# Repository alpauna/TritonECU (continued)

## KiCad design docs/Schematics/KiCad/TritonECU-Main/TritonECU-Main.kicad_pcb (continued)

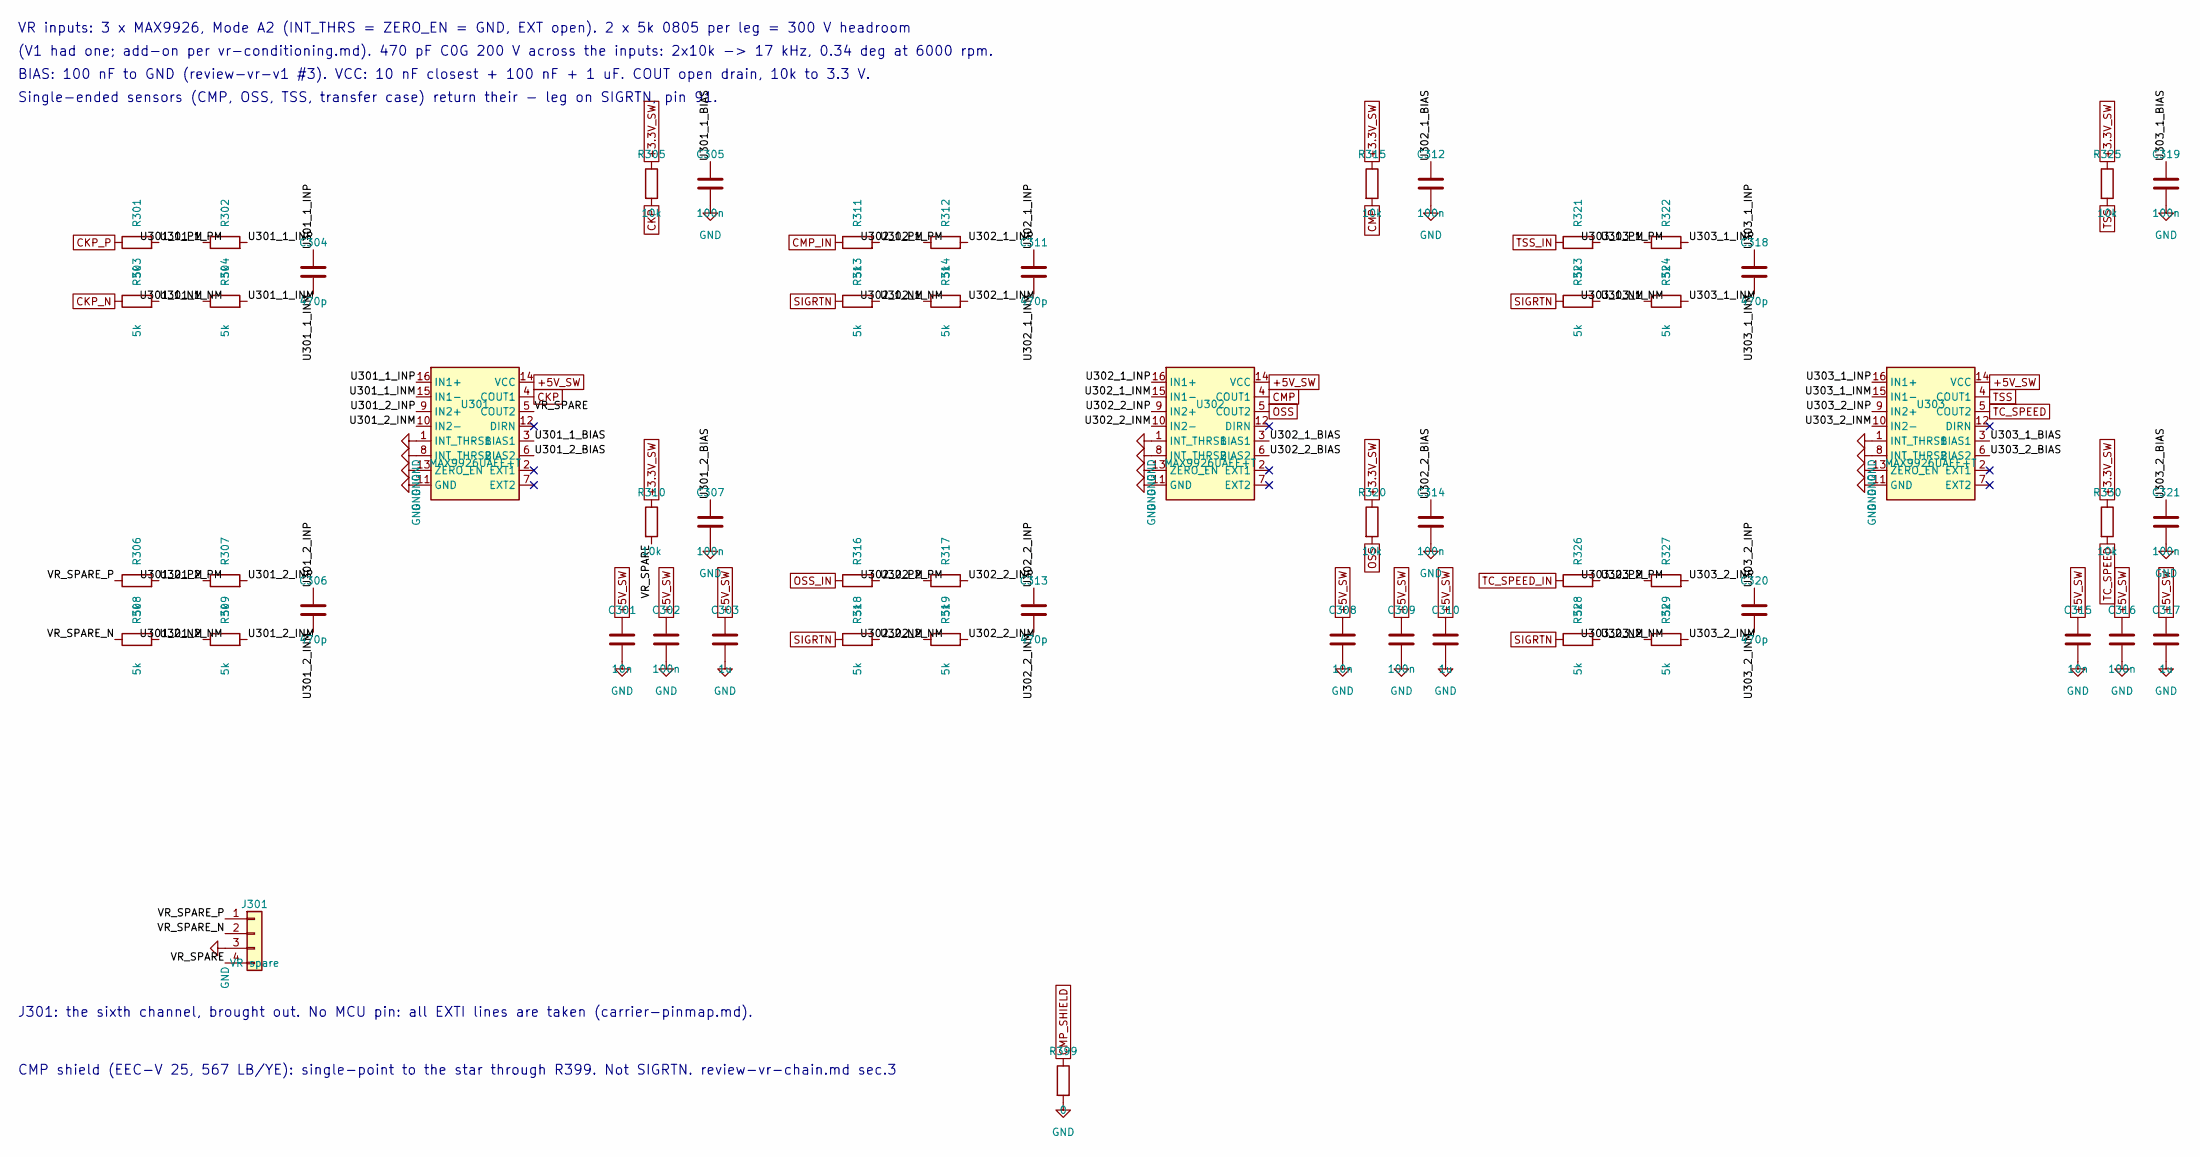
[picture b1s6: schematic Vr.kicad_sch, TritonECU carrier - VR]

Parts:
C301, C308, C315: 10n; C_0603_1608Metric_Pad1.08x0.95mm_HandSolder
C302, C305, C307, C309, C312, C314, C316, C319, C321: 100n; C_0603_1608Metric_Pad1.08x0.95mm_HandSolder
C303, C310, C317: 1u; C_0603_1608Metric_Pad1.08x0.95mm_HandSolder
C304, C306, C311, C313, C318, C320: 470p; C_0805_2012Metric_Pad1.18x1.45mm_HandSolder
J301: VR spare; PinHeader_1x04_P2.54mm_Vertical
R301, R302, R303, R304, R306, R307, R308, R309, R311, R312, R313, R314, R316, R317, R318, R319, R321, R322, R323, R324, R326, R327, R328, R329: 5k; R_0805_2012Metric_Pad1.20x1.40mm_HandSolder
R305, R310, R315, R320, R325, R330: 10k; R_0603_1608Metric_Pad0.98x0.95mm_HandSolder
R399: 0; R_0603_1608Metric_Pad0.98x0.95mm_HandSolder
U301, U302, U303: MAX9926UAEE+T; QSOP-16_3.9x4.9mm_P0.635mm

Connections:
+3.3V_SW: R305.1, R310.1, R315.1, R320.1, R325.1, R330.1; also elsewhere on the board
+5V_SW: C301.1, C302.1, C303.1, C308.1, C309.1, C310.1, C315.1, C316.1, C317.1, U301.14 (VCC), U302.14 (VCC), U303.14 (VCC); also elsewhere on the board
/VR/U301_1_BIAS: C305.1, U301.3 (BIAS1)
/VR/U301_1_INM: C304.2, R304.2, U301.15 (IN1-)
/VR/U301_1_INP: C304.1, R302.2, U301.16 (IN1+)
/VR/U301_1_NM: R303.2, R304.1
/VR/U301_1_PM: R301.2, R302.1
/VR/U301_2_BIAS: C307.1, U301.6 (BIAS2)
/VR/U301_2_INM: C306.2, R309.2, U301.10 (IN2-)
/VR/U301_2_INP: C306.1, R307.2, U301.9 (IN2+)
/VR/U301_2_NM: R308.2, R309.1
/VR/U301_2_PM: R306.2, R307.1
/VR/U302_1_BIAS: C312.1, U302.3 (BIAS1)
/VR/U302_1_INM: C311.2, R314.2, U302.15 (IN1-)
/VR/U302_1_INP: C311.1, R312.2, U302.16 (IN1+)
/VR/U302_1_NM: R313.2, R314.1
/VR/U302_1_PM: R311.2, R312.1
/VR/U302_2_BIAS: C314.1, U302.6 (BIAS2)
/VR/U302_2_INM: C313.2, R319.2, U302.10 (IN2-)
/VR/U302_2_INP: C313.1, R317.2, U302.9 (IN2+)
/VR/U302_2_NM: R318.2, R319.1
/VR/U302_2_PM: R316.2, R317.1
/VR/U303_1_BIAS: C319.1, U303.3 (BIAS1)
/VR/U303_1_INM: C318.2, R324.2, U303.15 (IN1-)
/VR/U303_1_INP: C318.1, R322.2, U303.16 (IN1+)
/VR/U303_1_NM: R323.2, R324.1
/VR/U303_1_PM: R321.2, R322.1
/VR/U303_2_BIAS: C321.1, U303.6 (BIAS2)
/VR/U303_2_INM: C320.2, R329.2, U303.10 (IN2-)
/VR/U303_2_INP: C320.1, R327.2, U303.9 (IN2+)
/VR/U303_2_NM: R328.2, R329.1
/VR/U303_2_PM: R326.2, R327.1
/VR/VR_SPARE: J301.4, R310.2, U301.5 (COUT2)
/VR/VR_SPARE_N: J301.2, R308.1
/VR/VR_SPARE_P: J301.1, R306.1
CKP: R305.2, U301.4 (COUT1); also elsewhere on the board
CKP_N: R303.1; also elsewhere on the board
CKP_P: R301.1; also elsewhere on the board
CMP: R315.2, U302.4 (COUT1); also elsewhere on the board
CMP_IN: R311.1; also elsewhere on the board
CMP_SHIELD: R399.1; also elsewhere on the board
GND: C301.2, C302.2, C303.2, C305.2, C307.2, C308.2, C309.2, C310.2, C312.2, C314.2, C315.2, C316.2, C317.2, C319.2, C321.2, J301.3, R399.2, U301.1 (INT_THRS1), U301.8 (INT_THRS2), U301.11 (GND), U301.13 (ZERO_EN), U302.1 (INT_THRS1), U302.8 (INT_THRS2), U302.11 (GND), U302.13 (ZERO_EN), U303.1 (INT_THRS1), U303.8 (INT_THRS2), U303.11 (GND), U303.13 (ZERO_EN); also elsewhere on the board
OSS: R320.2, U302.5 (COUT2); also elsewhere on the board
OSS_IN: R316.1; also elsewhere on the board
SIGRTN: R313.1, R318.1, R323.1, R328.1; also elsewhere on the board
TC_SPEED: R330.2, U303.5 (COUT2); also elsewhere on the board
TC_SPEED_IN: R326.1; also elsewhere on the board
TSS: R325.2, U303.4 (COUT1); also elsewhere on the board
TSS_IN: R321.1; also elsewhere on the board

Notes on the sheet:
VR inputs: 3 x MAX9926, Mode A2 (INT_THRS = ZERO_EN = GND, EXT open). 2 x 5k 0805 per leg = 300 V headroom
(V1 had one; add-on per vr-conditioning.md). 470 pF C0G 200 V across the inputs: 2x10k -> 17 kHz, 0.34 deg at 6000 rpm.
BIAS: 100 nF to GND (review-vr-v1 #3). VCC: 10 nF closest + 100 nF + 1 uF. COUT open drain, 10k to 3.3 V.
Single-ended sensors (CMP, OSS, TSS, transfer case) return their - leg on SIGRTN, pin 91.
J301: the sixth channel, brought out. No MCU pin: all EXTI lines are taken (carrier-pinmap.md).
CMP shield (EEC-V 25, 567 LB/YE): single-point to the star through R399. Not SIGRTN. review-vr-chain.md sec.3

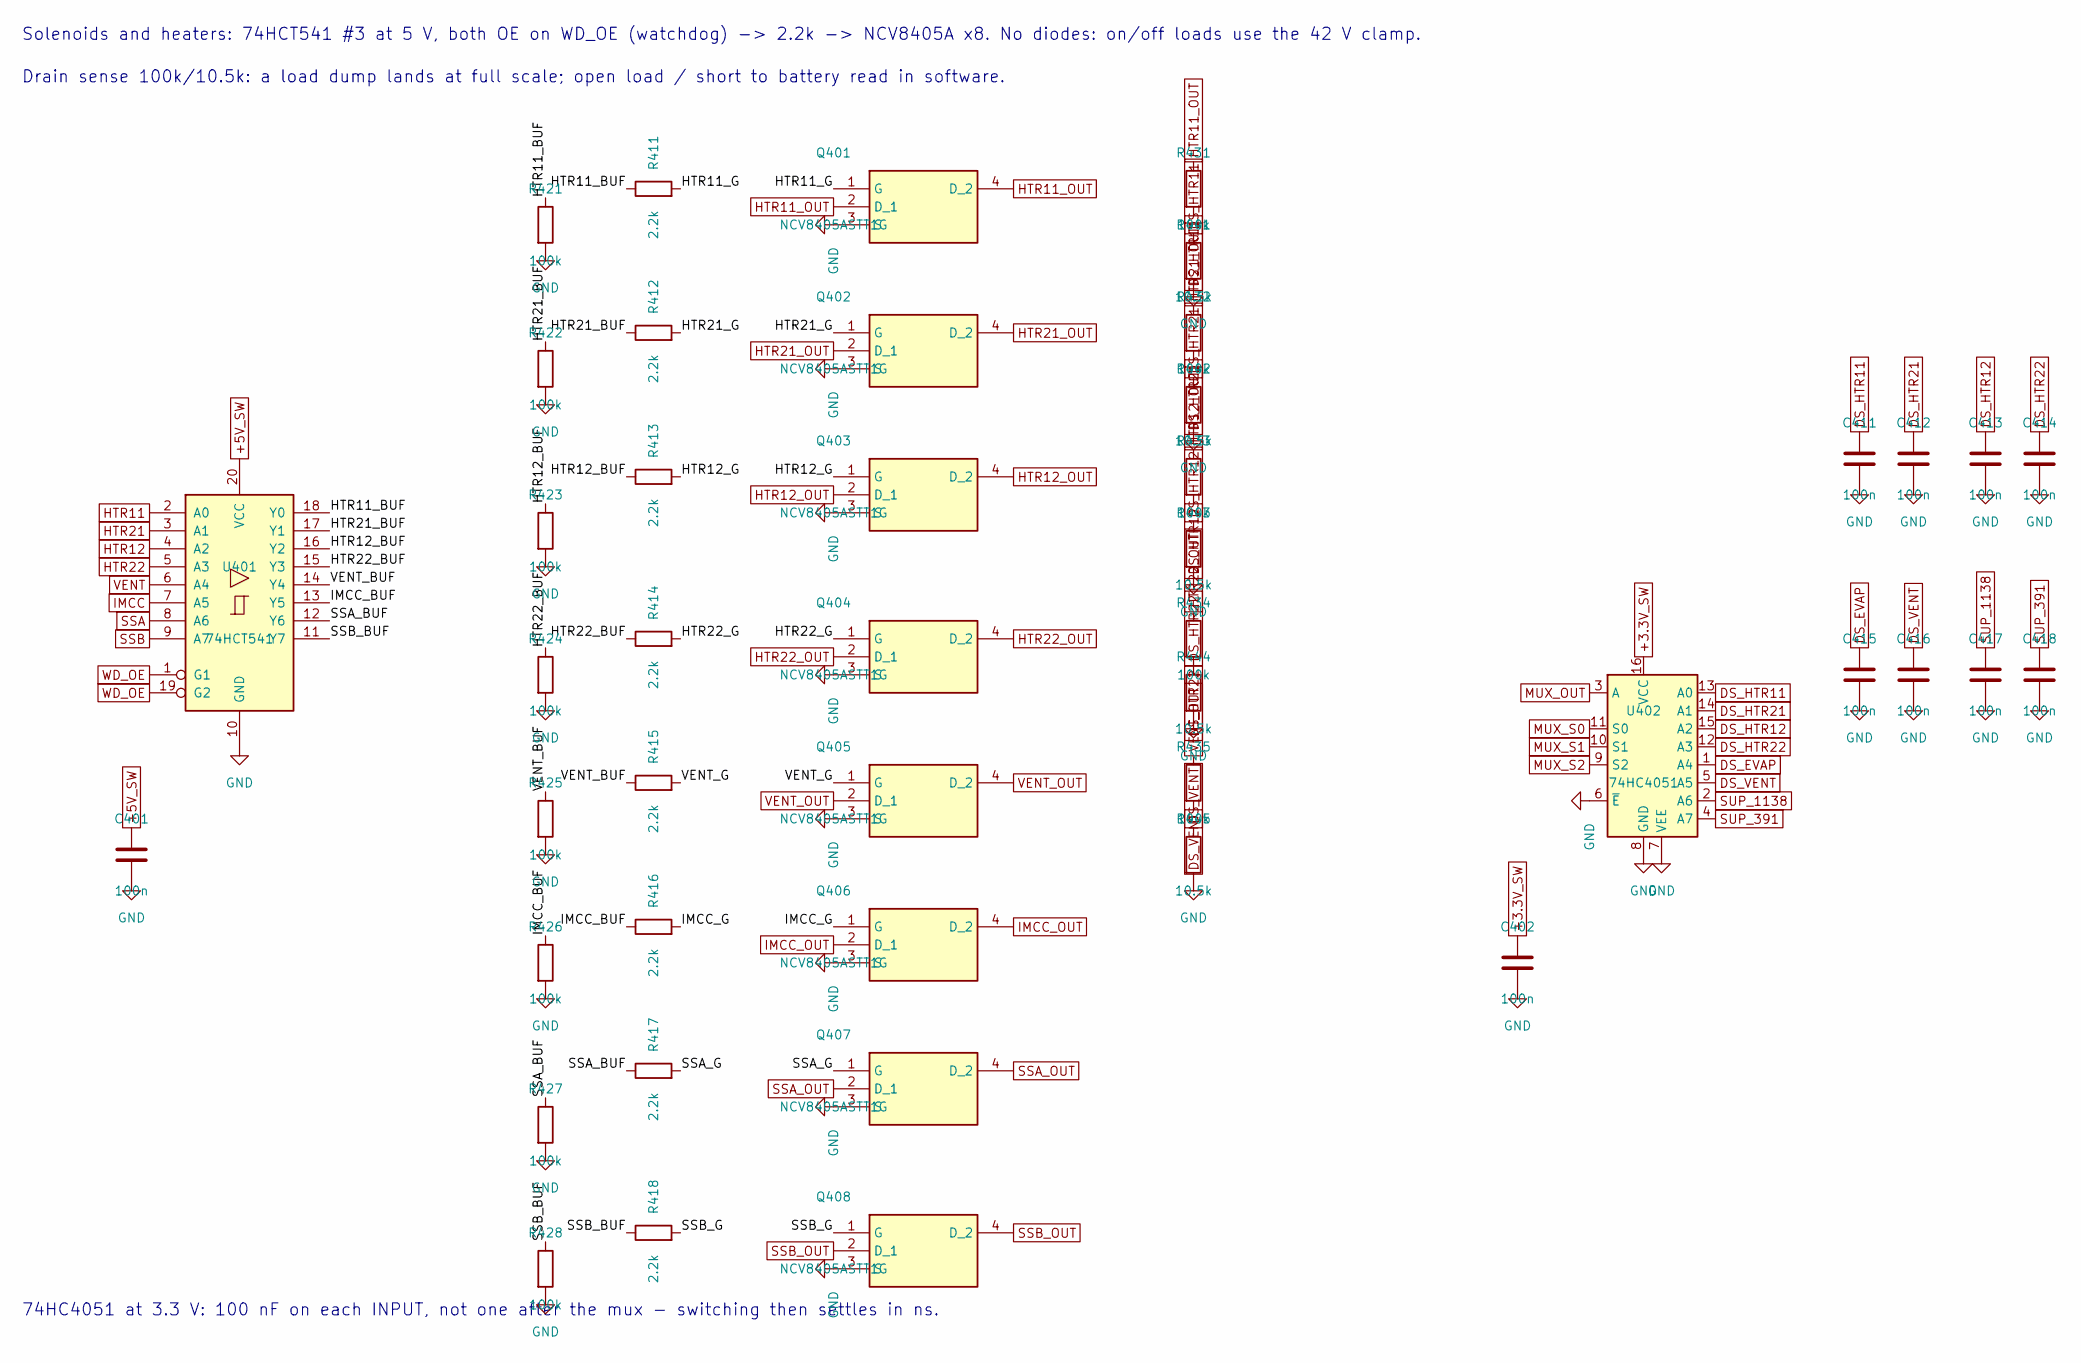
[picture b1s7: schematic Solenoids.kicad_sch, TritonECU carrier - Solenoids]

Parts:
C401, C402, C411, C412, C413, C414, C415, C416, C417, C418: 100n; C_0603_1608Metric_Pad1.08x0.95mm_HandSolder
Q401, Q402, Q403, Q404, Q405, Q406, Q407, Q408: NCV8405ASTT1G; SOT230P700X175-4N
R411, R412, R413, R414, R415, R416, R417, R418: 2.2k; R_0603_1608Metric_Pad0.98x0.95mm_HandSolder
R421, R422, R423, R424, R425, R426, R427, R428, R431, R432, R433, R434, R435: 100k; R_0603_1608Metric_Pad0.98x0.95mm_HandSolder
R441, R442, R443, R444, R445: 10.5k; R_0603_1608Metric_Pad0.98x0.95mm_HandSolder
U401: 74HCT541; SOIC-20W_7.5x12.8mm_P1.27mm
U402: 74HC4051; TSSOP-16_4.4x5mm_P0.65mm

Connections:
+3.3V_SW: C402.1, U402.16 (VCC); also elsewhere on the board
+5V_SW: C401.1, U401.20 (VCC); also elsewhere on the board
/Solenoids/HTR11_BUF: R411.1, R421.1, U401.18 (Y0)
/Solenoids/HTR11_G: Q401.1 (G), R411.2
/Solenoids/HTR12_BUF: R413.1, R423.1, U401.16 (Y2)
/Solenoids/HTR12_G: Q403.1 (G), R413.2
/Solenoids/HTR21_BUF: R412.1, R422.1, U401.17 (Y1)
/Solenoids/HTR21_G: Q402.1 (G), R412.2
/Solenoids/HTR22_BUF: R414.1, R424.1, U401.15 (Y3)
/Solenoids/HTR22_G: Q404.1 (G), R414.2
/Solenoids/IMCC_BUF: R416.1, R426.1, U401.13 (Y5)
/Solenoids/IMCC_G: Q406.1 (G), R416.2
/Solenoids/SSA_BUF: R417.1, R427.1, U401.12 (Y6)
/Solenoids/SSA_G: Q407.1 (G), R417.2
/Solenoids/SSB_BUF: R418.1, R428.1, U401.11 (Y7)
/Solenoids/SSB_G: Q408.1 (G), R418.2
/Solenoids/VENT_BUF: R415.1, R425.1, U401.14 (Y4)
/Solenoids/VENT_G: Q405.1 (G), R415.2
DS_EVAP: C415.1, U402.1 (A4); also elsewhere on the board
DS_HTR11: C411.1, R431.2, R441.1, U402.13 (A0)
DS_HTR12: C413.1, R433.2, R443.1, U402.15 (A2)
DS_HTR21: C412.1, R432.2, R442.1, U402.14 (A1)
DS_HTR22: C414.1, R434.2, R444.1, U402.12 (A3)
DS_VENT: C416.1, R435.2, R445.1, U402.5 (A5)
GND: C401.2, C402.2, C411.2, C412.2, C413.2, C414.2, C415.2, C416.2, C417.2, C418.2, Q401.3 (S), Q402.3 (S), Q403.3 (S), Q404.3 (S), Q405.3 (S), Q406.3 (S), Q407.3 (S), Q408.3 (S), R421.2, R422.2, R423.2, R424.2, R425.2, R426.2, R427.2, R428.2, R441.2, R442.2, R443.2, R444.2, R445.2, U401.10 (GND), U402.6 (~E), U402.7 (VEE), U402.8 (GND); also elsewhere on the board
HTR11: U401.2 (A0); also elsewhere on the board
HTR11_OUT: Q401.2 (D_1), Q401.4 (D_2), R431.1; also elsewhere on the board
HTR12: U401.4 (A2); also elsewhere on the board
HTR12_OUT: Q403.2 (D_1), Q403.4 (D_2), R433.1; also elsewhere on the board
HTR21: U401.3 (A1); also elsewhere on the board
HTR21_OUT: Q402.2 (D_1), Q402.4 (D_2), R432.1; also elsewhere on the board
HTR22: U401.5 (A3); also elsewhere on the board
HTR22_OUT: Q404.2 (D_1), Q404.4 (D_2), R434.1; also elsewhere on the board
IMCC: U401.7 (A5); also elsewhere on the board
IMCC_OUT: Q406.2 (D_1), Q406.4 (D_2); also elsewhere on the board
MUX_OUT: U402.3 (A); also elsewhere on the board
MUX_S0: U402.11 (S0); also elsewhere on the board
MUX_S1: U402.10 (S1); also elsewhere on the board
MUX_S2: U402.9 (S2); also elsewhere on the board
SSA: U401.8 (A6); also elsewhere on the board
SSA_OUT: Q407.2 (D_1), Q407.4 (D_2); also elsewhere on the board
SSB: U401.9 (A7); also elsewhere on the board
SSB_OUT: Q408.2 (D_1), Q408.4 (D_2); also elsewhere on the board
SUP_391: C418.1, U402.4 (A7); also elsewhere on the board
SUP_1138: C417.1, U402.2 (A6); also elsewhere on the board
VENT: U401.6 (A4); also elsewhere on the board
VENT_OUT: Q405.2 (D_1), Q405.4 (D_2), R435.1; also elsewhere on the board
WD_OE: U401.1 (G1), U401.19 (G2); also elsewhere on the board

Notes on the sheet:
Solenoids and heaters: 74HCT541 #3 at 5 V, both OE on WD_OE (watchdog) -> 2.2k -> NCV8405A x8. No diodes: on/off loads use the 42 V clamp.
Drain sense 100k/10.5k: a load dump lands at full scale; open load / short to battery read in software.
74HC4051 at 3.3 V: 100 nF on each INPUT, not one after the mux - switching then settles in ns.

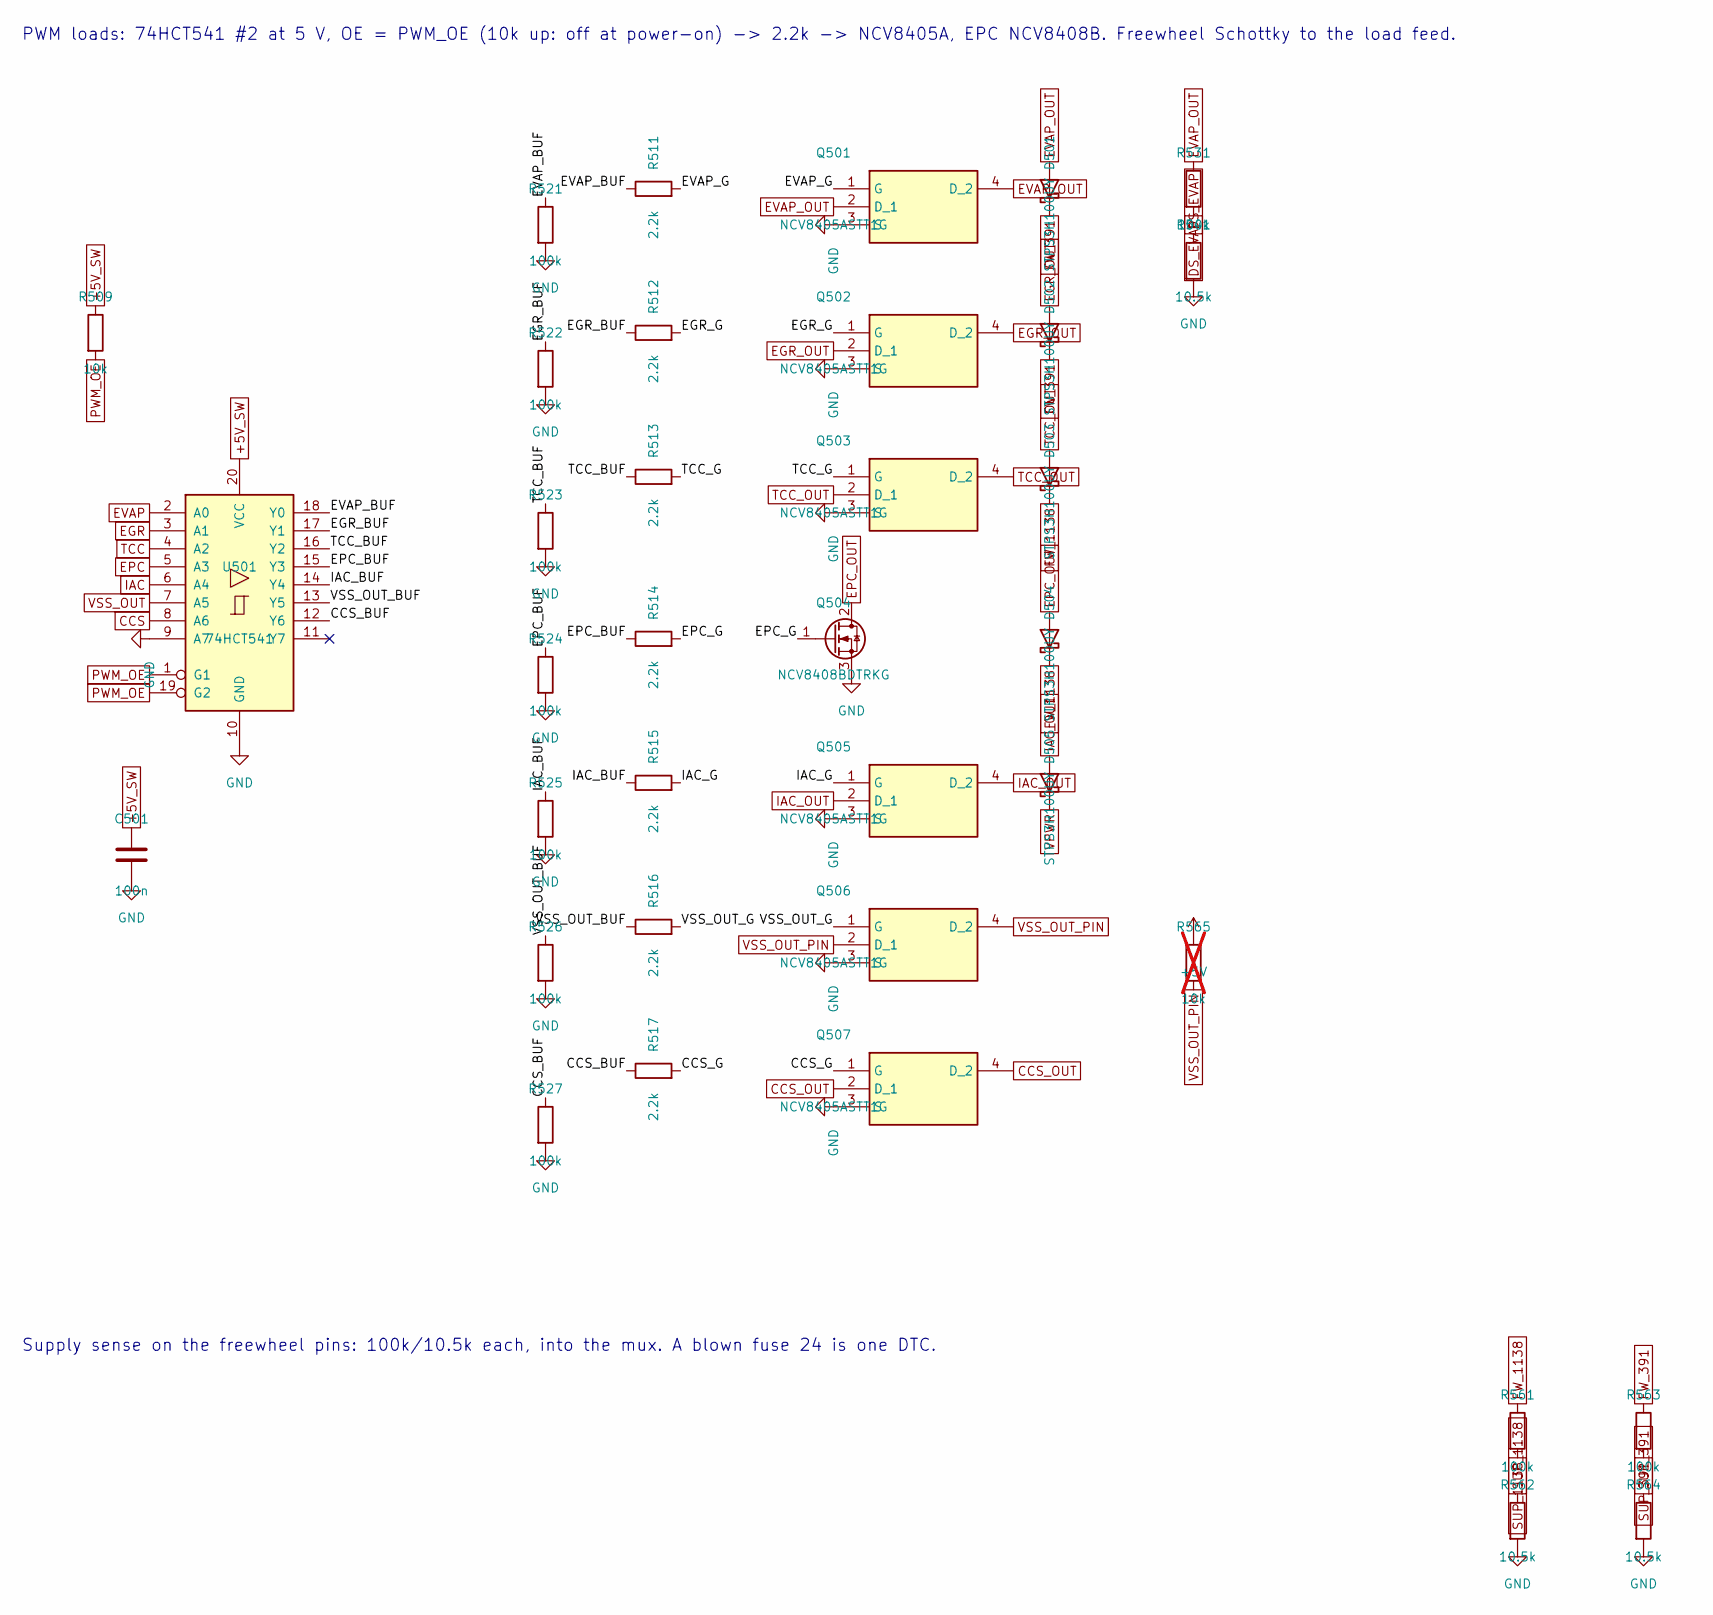
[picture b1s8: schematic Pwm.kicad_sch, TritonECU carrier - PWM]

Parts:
C501: 100n; C_0603_1608Metric_Pad1.08x0.95mm_HandSolder
D501, D502, D503, D504, D505: STPS3H100UY; D_SMB
Q501, Q502, Q503, Q505, Q506, Q507: NCV8405ASTT1G; SOT230P700X175-4N
Q504: NCV8408BDTRKG; TO-252-2
R509: 10k; R_0603_1608Metric_Pad0.98x0.95mm_HandSolder
R511, R512, R513, R514, R515, R516, R517: 2.2k; R_0603_1608Metric_Pad0.98x0.95mm_HandSolder
R521, R522, R523, R524, R525, R526, R527, R531, R561, R563: 100k; R_0603_1608Metric_Pad0.98x0.95mm_HandSolder
R541, R562, R564: 10.5k; R_0603_1608Metric_Pad0.98x0.95mm_HandSolder
R565: 10k; R_0603_1608Metric_Pad0.98x0.95mm_HandSolder; not fitted
U501: 74HCT541; SOIC-20W_7.5x12.8mm_P1.27mm

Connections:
+5V: R565.1; also elsewhere on the board
+5V_SW: C501.1, R509.1, U501.20 (VCC); also elsewhere on the board
/PWM/CCS_BUF: R517.1, R527.1, U501.12 (Y6)
/PWM/CCS_G: Q507.1 (G), R517.2
/PWM/EGR_BUF: R512.1, R522.1, U501.17 (Y1)
/PWM/EGR_G: Q502.1 (G), R512.2
/PWM/EPC_BUF: R514.1, R524.1, U501.15 (Y3)
/PWM/EPC_G: Q504.1 (G), R514.2
/PWM/EVAP_BUF: R511.1, R521.1, U501.18 (Y0)
/PWM/EVAP_G: Q501.1 (G), R511.2
/PWM/IAC_BUF: R515.1, R525.1, U501.14 (Y4)
/PWM/IAC_G: Q505.1 (G), R515.2
/PWM/TCC_BUF: R513.1, R523.1, U501.16 (Y2)
/PWM/TCC_G: Q503.1 (G), R513.2
/PWM/VSS_OUT_BUF: R516.1, R526.1, U501.13 (Y5)
/PWM/VSS_OUT_G: Q506.1 (G), R516.2
CCS: U501.8 (A6); also elsewhere on the board
CCS_OUT: Q507.2 (D_1), Q507.4 (D_2); also elsewhere on the board
DS_EVAP: R531.2, R541.1; also elsewhere on the board
EGR: U501.3 (A1); also elsewhere on the board
EGR_OUT: D502.2 (A), Q502.2 (D_1), Q502.4 (D_2); also elsewhere on the board
EPC: U501.5 (A3); also elsewhere on the board
EPC_OUT: D504.2 (A), Q504.2 (D); also elsewhere on the board
EVAP: U501.2 (A0); also elsewhere on the board
EVAP_OUT: D501.2 (A), Q501.2 (D_1), Q501.4 (D_2), R531.1; also elsewhere on the board
FW_391: D501.1 (K), D502.1 (K), R563.1; also elsewhere on the board
FW_1138: D503.1 (K), D504.1 (K), R561.1; also elsewhere on the board
GND: C501.2, Q501.3 (S), Q502.3 (S), Q503.3 (S), Q504.3 (S), Q505.3 (S), Q506.3 (S), Q507.3 (S), R521.2, R522.2, R523.2, R524.2, R525.2, R526.2, R527.2, R541.2, R562.2, R564.2, U501.9 (A7), U501.10 (GND); also elsewhere on the board
IAC: U501.6 (A4); also elsewhere on the board
IAC_OUT: D505.2 (A), Q505.2 (D_1), Q505.4 (D_2); also elsewhere on the board
PWM_OE: R509.2, U501.1 (G1), U501.19 (G2); also elsewhere on the board
SUP_391: R563.2, R564.1; also elsewhere on the board
SUP_1138: R561.2, R562.1; also elsewhere on the board
TCC: U501.4 (A2); also elsewhere on the board
TCC_OUT: D503.2 (A), Q503.2 (D_1), Q503.4 (D_2); also elsewhere on the board
VPWR: D505.1 (K); also elsewhere on the board
VSS_OUT: U501.7 (A5); also elsewhere on the board
VSS_OUT_PIN: Q506.2 (D_1), Q506.4 (D_2), R565.2; also elsewhere on the board

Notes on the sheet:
PWM loads: 74HCT541 #2 at 5 V, OE = PWM_OE (10k up: off at power-on) -> 2.2k -> NCV8405A, EPC NCV8408B. Freewheel Schottky to the load feed.
Supply sense on the freewheel pins: 100k/10.5k each, into the mux. A blown fuse 24 is one DTC.

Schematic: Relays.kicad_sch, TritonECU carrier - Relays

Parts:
C601: 100n; C_0805_2012Metric_Pad1.18x1.45mm_HandSolder
F601, F602, F603, F604: MF-MSMF030/60-2; Fuse_1812_4532Metric
R601, R602, R603, R604: 100k; R_0603_1608Metric_Pad0.98x0.95mm_HandSolder
U601: TBD62083AFNG; SOP65P640X155-18N

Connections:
/Relays/ACC_SINK: F604.1, U601.15 (O4)
/Relays/FAN1_SINK: F602.1, U601.17 (O2)
/Relays/FAN2_SINK: F603.1, U601.16 (O3)
/Relays/FPUMP_SINK: F601.1, U601.18 (O1)
ACC: R604.1, U601.4 (I4); also elsewhere on the board
ACC_OUT: F604.2; also elsewhere on the board
FAN1: R602.1, U601.2 (I2); also elsewhere on the board
FAN1_OUT: F602.2; also elsewhere on the board
FAN2: R603.1, U601.3 (I3); also elsewhere on the board
FAN2_OUT: F603.2; also elsewhere on the board
FPUMP: R601.1, U601.1 (I1); also elsewhere on the board
FPUMP_OUT: F601.2; also elsewhere on the board
GND: C601.2, R601.2, R602.2, R603.2, R604.2, U601.5 (I5), U601.6 (I6), U601.7 (I7), U601.8 (I8), U601.9 (GND); also elsewhere on the board
VBAT_SENSE: C601.1, U601.10 (COMMON); also elsewhere on the board

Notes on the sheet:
Relays: TBD62083AFNG, direct from GPIO. 100k pulldown holds every relay off through reset.
COMMON = permanent B+ (EEC-V 55, 729 RD/WH, CJB 5 A): every coil feed is at or below it, so no channel
back-feeds. [CONFIRM] sharing pin 55 with the battery-sense divider: clamp current is only the coil decay.
PTC in series: the array has no current limit, so a shorted coil is stopped by F60x. Coil currents [CONFIRM] on the truck.
Channels 5-8 spare: inputs to GND, outputs open. No MCU pins left for them (carrier-pinmap.md).

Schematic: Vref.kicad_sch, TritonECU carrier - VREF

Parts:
C701: 1u; C_0805_2012Metric_Pad1.18x1.45mm_HandSolder
C702, C704, C705, C706: 100n; C_0603_1608Metric_Pad1.08x0.95mm_HandSolder
C703: 22u; C_1206_3216Metric_Pad1.33x1.80mm_HandSolder
C707: 100n; C_0603_1608Metric_Pad1.08x0.95mm_HandSolder; not fitted
C708: 22n; C_0603_1608Metric_Pad1.08x0.95mm_HandSolder
C709: 22n; C_0603_1608Metric_Pad1.08x0.95mm_HandSolder; not fitted
C710: 10n; C_0603_1608Metric_Pad1.08x0.95mm_HandSolder
D701: SMAJ24CA; D_SMA
D702: SMAJ24CA; D_SMA; not fitted
D703, D704: BAT54J; D_SOD-323F
Q701: DMN6040SVTQ-7; SOT95P280X100-6N
Q702: DMN6040SVTQ-7; SOT95P280X100-6N; not fitted
R701, R708: 100k; R_0603_1608Metric_Pad0.98x0.95mm_HandSolder
R702, R703, R704: 10k; R_0603_1608Metric_Pad0.98x0.95mm_HandSolder
R705: 2.2k; R_0603_1608Metric_Pad0.98x0.95mm_HandSolder
R706: 4.7k; R_0603_1608Metric_Pad0.98x0.95mm_HandSolder
R707: 8.06k; R_0603_1608Metric_Pad0.98x0.95mm_HandSolder
R709: 12.4k; R_0603_1608Metric_Pad0.98x0.95mm_HandSolder
TP701: VREF2; TestPoint_Pad_D1.5mm; not fitted
U701: NCV8772CDT504RKG; TO-252-5_TabPin3
U702: TPS2H160BQPWPRQ1; SOP65P640X120-17N
U703: LM74700QDBVRQ1; SOT-23-6
U704: LM74700QDBVRQ1; SOT-23-6; not fitted

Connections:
+3.3V: D703.1 (K), D704.1 (K); also elsewhere on the board
+3.3V_SW: R704.1; also elsewhere on the board
/VREF/VREF1_G: Q701.3 (G), U703.5 (GATE)
/VREF/VREF1_SW: C706.2, C708.1, Q701.4 (S), U702.15 (OUT1_1), U702.16 (OUT1_2), U703.3 (EN), U703.6 (ANODE)
/VREF/VREF1_VCAP: C706.1, U703.1 (VCAP)
/VREF/VREF2: D702.1 (A1), Q702.1 (D_1), Q702.2 (D_2), Q702.5 (D_3), Q702.6 (D_4), TP701.1, U704.4 (CATHODE)
/VREF/VREF2_G: Q702.3 (G), U704.5 (GATE)
/VREF/VREF2_SW: C707.2, C709.1, Q702.4 (S), U702.11 (OUT2_1), U702.12 (OUT2_2), U704.3 (EN), U704.6 (ANODE)
/VREF/VREF2_VCAP: C707.1, U704.1 (VCAP)
/VREF/VREF_CL: R707.1, U702.7 (CL)
/VREF/VREF_CS_RAW: R705.1, R706.1, U702.6 (CS)
/VREF/VREF_DIAG: R702.2, U702.3 (DIAG_EN)
/VREF/VREF_THER: R703.2, U702.9 (THER)
GND: C701.2, C702.2, C703.2, C704.2, C705.2, C708.2, C709.2, C710.2, D701.2 (A2), D702.2 (A2), R701.2, R705.2, R707.2, R709.2, U701.3 (GND), U702.8 (GND), U702.17 (EP), U703.2 (GND), U704.2 (GND); also elsewhere on the board
VPROT: C701.1, C702.1, U701.1 (VIN); also elsewhere on the board
VREF: D701.1 (A1), Q701.1 (D_1), Q701.2 (D_2), Q701.5 (D_3), Q701.6 (D_4), R708.1, U703.4 (CATHODE); also elsewhere on the board
VREF_5V: C703.1, C704.1, C705.1, R702.1, R703.1, U701.5 (VOUT), U702.13 (VS_1), U702.14 (VS_2); also elsewhere on the board
VREF_CS: D703.2 (A), R706.2; also elsewhere on the board
VREF_EN: R701.1, U701.4 (EN); also elsewhere on the board
VREF_FAULT: R704.2, U702.4 (~FAULT); also elsewhere on the board
VREF_IN1: U702.1 (IN1); also elsewhere on the board
VREF_IN2: U702.2 (IN2); also elsewhere on the board
VREF_SEL: U702.5 (SEL); also elsewhere on the board
VREF_STB: C710.1, D704.2 (A), R708.2, R709.1; also elsewhere on the board

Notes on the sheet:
VREF: NCV8772C 5.00 V on VPROT (the LTC4364 output, not the 5 V buck-boost), EN under MCU control.
TPS2H160B-Q1: RCL 8.06k = 248 mA per feed; RCS 2.2k (2.5 V linear ceiling at VS = 5 V); THER high = latch.
LM74700-Q1 + DMN6040 (VGS +-20 V) blocks a short to battery; SMAJ24CA stands off 24 V, transients only. No PPTC.
Firmware sheds a faulted channel (t_CL deg 80-180 us), retries seconds apart. Hold IN1/IN2/SEL low while EN is low.
VREF_5V is the ratiometric divisor: the ADS8588H senses it here, one channel for both feeds.
Channel 2 (U704, Q702, D702, TP701) not fitted: this truck has one VREF pin, 90. Never enable IN2.
Short to battery: 100k/12.4k from the feed. 5 V -> 0.55 V, 14 V -> 1.54 V, 27 V -> 2.98 V. Returns to the ADC ground.

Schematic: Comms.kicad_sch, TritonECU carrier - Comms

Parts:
C901, C903, C904, C905, C907, C914: 100n; C_0603_1608Metric_Pad1.08x0.95mm_HandSolder
C902, C909, C911: 1u; C_0603_1608Metric_Pad1.08x0.95mm_HandSolder
C906, C913: 4.7u; C_0805_2012Metric_Pad1.18x1.45mm_HandSolder
C908, C910: 4.7n; C_0603_1608Metric_Pad1.08x0.95mm_HandSolder
C912: 1n; C_0603_1608Metric_Pad1.08x0.95mm_HandSolder
D901, D905: NUP2105L; SOT-23
D902, D903: MM3Z3V3BW; D_SOD-323F
D904: SMF3.3A; D_SMF
J901: USB4105-GF-A; USB_C_Receptacle_GCT_USB4105-xx-A_16P_TopMnt_Horizontal
J902: 104031-0811; microSD_HC_Molex_104031-0811
R901: 10k; R_0603_1608Metric_Pad0.98x0.95mm_HandSolder
R902, R903, R909, R918: 100; R_0603_1608Metric_Pad0.98x0.95mm_HandSolder
R904, R905, R906, R907, R919: 100k; R_0603_1608Metric_Pad0.98x0.95mm_HandSolder
R908: 4.7M; R_0603_1608Metric_Pad0.98x0.95mm_HandSolder
R910: 0; R_0603_1608Metric_Pad0.98x0.95mm_HandSolder
R911, R912: 60.4; R_1206_3216Metric_Pad1.30x1.75mm_HandSolder
R913, R914: 5.1k; R_0603_1608Metric_Pad0.98x0.95mm_HandSolder
R915: 15k; R_0603_1608Metric_Pad0.98x0.95mm_HandSolder
R916: 27k; R_0603_1608Metric_Pad0.98x0.95mm_HandSolder
R917: 1M; R_0603_1608Metric_Pad0.98x0.95mm_HandSolder
R920: 22; R_0603_1608Metric_Pad0.98x0.95mm_HandSolder
R921, R922, R923, R924, R925: 47k; R_0603_1608Metric_Pad0.98x0.95mm_HandSolder
U901: DRV8837DSGR; Texas_DSG0008A_WSON-8-1EP_2x2mm_P0.5mm_EP0.9x1.6mm
U902: TLV7031DBVR; SOT-23-5
U903: TJA1042T/3; SOIC-8_3.9x4.9mm_P1.27mm
U904: USBLC6-2SC6; SOT-23-6
U905: TPS22917DBVR; SOT-23-6

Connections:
+3.3V: C903.1, C904.1, C907.1, C911.1, U901.8 (VCC), U902.5 (V+), U903.5 (VIO), U905.1 (VIN); also elsewhere on the board
+5V: C901.1, C902.1, C905.1, C906.1, U901.1 (VM), U903.3 (VCC); also elsewhere on the board
/Comms/CAN_SPLIT: C908.1, R911.2, R912.1
/Comms/SCP_CMP: R908.1, R909.1, U902.1
/Comms/SCP_RXN: D903.1 (K), R906.2, R907.1, U902.4 (-)
/Comms/SCP_RXP: D902.1 (K), R904.2, R905.1, R908.2, U902.3 (+)
/Comms/SCP_TXN: R903.1, U901.3 (OUT2)
/Comms/SCP_TXP: R902.1, U901.2 (OUT1)
/Comms/SD_3V3: C913.1, C914.1, J902.4 (VDD), R918.2, R921.1, R922.1, R923.1, R924.1, R925.1, U905.6 (VOUT)
/Comms/SD_CLK: J902.5 (CLK), R920.2
/Comms/SD_CT: C912.1, U905.4 (CT)
/Comms/SD_D1: J902.8 (DAT1), R923.2
/Comms/SD_D2: J902.1 (DAT2), R924.2
/Comms/SD_D3: J902.2 (DAT3/CD), R925.2
/Comms/SD_QOD: R918.1, U905.5 (QOD)
/Comms/USB_CC1: J901.A5 (CC1), R913.1
/Comms/USB_CC2: J901.B5 (CC2), R914.1
/Comms/USB_SHIELD: C910.1, J901.SH (SHIELD), R917.1
/Comms/USB_VBUS_C: C909.1, J901.A4 (VBUS), J901.A9 (VBUS), J901.B4 (VBUS), J901.B9 (VBUS), R915.1, U904.5 (VBUS)
CAN_H: D905.1 (K), R911.1, U903.7 (CANH); also elsewhere on the board
CAN_L: D905.2 (K), R912.2, U903.6 (CANL); also elsewhere on the board
CAN_RX: R910.1, U903.4 (RXD); also elsewhere on the board
CAN_RX_WAKE: R910.2; also elsewhere on the board
CAN_STB: U903.8 (STB); also elsewhere on the board
CAN_TX: U903.1 (TXD); also elsewhere on the board
GND: C901.2, C902.2, C903.2, C904.2, C905.2, C906.2, C907.2, C908.2, C909.2, C910.2, C911.2, C912.2, C913.2, C914.2, D901.3 (A), D902.2 (A), D903.2 (A), D904.2 (A), D905.3 (A), J901.A1 (GND), J901.A12 (GND), J901.B1 (GND), J901.B12 (GND), J902.6 (VSS), J902.SH (SHIELD), R901.2, R905.2, R907.2, R913.2, R914.2, R916.2, R917.2, R919.2, U901.4 (GND), U901.9 (GND), U902.2 (V-), U903.2 (GND), U904.2 (GND), U905.2 (GND); also elsewhere on the board
J1850_NSLEEP: R901.1, U901.7 (~SLEEP); also elsewhere on the board
J1850_RX: D904.1 (K), R909.2; also elsewhere on the board
J1850_TXN: U901.5 (IN2); also elsewhere on the board
J1850_TXP: U901.6 (IN1); also elsewhere on the board
SCP_N: D901.2 (K), R903.2, R906.1; also elsewhere on the board
SCP_P: D901.1 (K), R902.2, R904.1; also elsewhere on the board
SD_CK: R920.1; also elsewhere on the board
SD_CMD: J902.3 (CMD), R921.2; also elsewhere on the board
SD_D0: J902.7 (DAT0), R922.2; also elsewhere on the board
SD_PWR_EN: R919.1, U905.3 (ON); also elsewhere on the board
USB_DM: J901.A7 (D-), J901.B7 (D-), U904.3 (I/O2), U904.4 (I/O2); also elsewhere on the board
USB_DP: J901.A6 (D+), J901.B6 (D+), U904.1 (I/O1), U904.6 (I/O1); also elsewhere on the board
USB_VBUS: R915.2, R916.1; also elsewhere on the board

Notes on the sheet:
SCP (J1850 PWM, EEC-V 16 = SCP+, 15 = SCP-): DRV8837 drives, TLV7031 receives. Passive state is IN1 = IN2 = LOW (coast,
Hi-Z) so another node can win arbitration; nSLEEP 10k low releases the whole bus at power-on. 100R per TX line.
RX divider 100k:100k BOTH to GND (not 10k:100k, not to 3.3 V: the two OpenJ1850 traps), MM3Z3V3 clamps, 4.7M hysteresis.
CAN (private, to the dash display; EEC-V 42 = CAN_H, 43 = CAN_L, terminals added): TJA1042T/3, 10 uA standby.
RXD goes to CAN1_RX (PD0) AND to PA0/WKUP1 through R9xx: Standby wakes only on a WKUP pin. STB has an internal pull-up.
TERMINATION - this ECU is a bus END. Split, matched 1 %: 2 x 60.4R + 4.7n. A THIRD node must NOT terminate.
USB-C, device only (tuning, flashing): 5.1k on CC1/CC2, USBLC6-2SC6, VBUS sensed only (never powers the ECU).
microSD, SDMMC2 1-bit. Card power through TPS22917 on SD_PWR_EN (100k down): 3.3 V is always on and an idle
card alone is ~100 uA against the 184 uA parked budget. Pull-ups go to the CARD rail so nothing back-powers it. No CD pin.
DAT3 pulled up keeps the card in SD mode (low at CMD0 selects SPI). DAT1/DAT2 unused in 1-bit, pulled up.

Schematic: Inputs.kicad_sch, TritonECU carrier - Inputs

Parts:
C1001, C1002, C1003, C1004, C1005, C1006, C1007, C1008: 10n; C_0603_1608Metric_Pad1.08x0.95mm_HandSolder
C1009: 100n; C_0603_1608Metric_Pad1.08x0.95mm_HandSolder
D1001, D1003, D1005, D1007, D1009, D1011, D1013, D1015: SMF24A; D_SMF
D1002, D1004, D1006, D1008, D1010, D1012, D1014, D1016, D1017: BAT54J; D_SOD-323F
J1001: TACH/SPEED; PinHeader_1x03_P2.54mm_Vertical
JP1001: BOOT0 DFU; SolderJumper-2_P1.3mm_Open_RoundedPad1.0x1.5mm
R1001, R1004, R1007, R1010: 4.7k; R_0805_2012Metric_Pad1.20x1.40mm_HandSolder
R1002, R1005, R1008, R1011, R1014, R1017, R1020, R1023, R1025: 33k; R_0805_2012Metric_Pad1.20x1.40mm_HandSolder
R1003, R1006, R1009, R1012, R1015, R1018, R1021, R1024, R1026: 15k; R_0603_1608Metric_Pad0.98x0.95mm_HandSolder
R1013, R1016, R1019, R1022: 4.7k; R_0805_2012Metric_Pad1.20x1.40mm_HandSolder; not fitted
R1027, R1028: 220; R_0603_1608Metric_Pad0.98x0.95mm_HandSolder

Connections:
4X4L: C1004.1, D1008.2 (A), R1011.2, R1012.1; also elsewhere on the board
4X4L_IN: D1007.1 (K), R1010.2, R1011.1; also elsewhere on the board
+3.3V: D1002.1 (K), D1004.1 (K), D1006.1 (K), D1008.1 (K), D1010.1 (K), D1012.1 (K), D1014.1 (K), D1016.1 (K), D1017.1 (K), JP1001.1 (A); also elsewhere on the board
/Inputs/SPEED_H: J1001.2, R1028.2
/Inputs/TACH_H: J1001.1, R1027.2
ACP: C1007.1, D1014.2 (A), R1020.2, R1021.1; also elsewhere on the board
ACP_IN: D1013.1 (K), R1019.2, R1020.1; also elsewhere on the board
BOOT0: JP1001.2 (B); also elsewhere on the board
BRAKE: C1006.1, D1012.2 (A), R1017.2, R1018.1; also elsewhere on the board
BRAKE_IN: D1011.1 (K), R1016.2, R1017.1; also elsewhere on the board
GND: C1001.2, C1002.2, C1003.2, C1004.2, C1005.2, C1006.2, C1007.2, C1008.2, C1009.2, D1001.2 (A), D1003.2 (A), D1005.2 (A), D1007.2 (A), D1009.2 (A), D1011.2 (A), D1013.2 (A), D1015.2 (A), J1001.3, R1003.2, R1006.2, R1009.2, R1012.2, R1015.2, R1018.2, R1021.2, R1024.2, R1026.2; also elsewhere on the board
IGN_WAKE: C1009.1, D1017.2 (A), R1025.2, R1026.1; also elsewhere on the board
SPEED: R1028.1; also elsewhere on the board
TACH: R1027.1; also elsewhere on the board
TCS: C1008.1, D1016.2 (A), R1023.2, R1024.1; also elsewhere on the board
TCS_IN: D1015.1 (K), R1022.2, R1023.1; also elsewhere on the board
TR1: C1001.1, D1002.2 (A), R1002.2, R1003.1; also elsewhere on the board
TR1_IN: D1001.1 (K), R1001.2, R1002.1; also elsewhere on the board
TR2: C1002.1, D1004.2 (A), R1005.2, R1006.1; also elsewhere on the board
TR2_IN: D1003.1 (K), R1004.2, R1005.1; also elsewhere on the board
TR3A: C1005.1, D1010.2 (A), R1014.2, R1015.1; also elsewhere on the board
TR3A_IN: D1009.1 (K), R1013.2, R1014.1; also elsewhere on the board
TR4: C1003.1, D1006.2 (A), R1008.2, R1009.1; also elsewhere on the board
TR4_IN: D1005.1 (K), R1007.2, R1008.1; also elsewhere on the board
VPWR: R1001.1, R1004.1, R1007.1, R1010.1, R1013.1, R1016.1, R1019.1, R1022.1, R1025.1; also elsewhere on the board

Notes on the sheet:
Switch inputs. One network: [4.7k pull-up to VPWR, ground-switched only] - SMF24A - 33k - node (15k, 10n, BAT54J to 3.3 V) - MCU.
Pull-ups go to VPWR, not 5 V / 3.3 V: those stay up parked, and a TR bit closed in Park would draw mA all night.
Levels: 14 V -> clamped; 9 V cranking -> 2.8 V (high-side) / 2.6 V (ground-switched) vs VIH 2.3 V. Open high-side reads 0.
TR3A (64): on this 4R70W it is 12 V cranking in P/N, so the high-side network. A 4R100 (270R coded) needs a 2.2k
pull-up to 3.3 V and 1k series instead - 4r100-deltas.md. Brake 92 is hot-at-all-times: 12 V when pressed.
TR1 (ground-switched)
TR2 (ground-switched)
TR4 (ground-switched)
4X4L (ground-switched)
TR3A (12 V high-side)
BRAKE (12 V high-side)
ACP (12 V high-side)
TCS (12 V high-side)
Key-on: VPWR (EEC relay, 361 RD) through the same divider to PC13 / WKUP4 - Standby wakes only on a WKUP pin.
100 nF, not 10 nF: a wake input should ignore ms-scale harness spikes. Also key-off detect while running.
TACH / SPEED: software square waves for the bench (gauge testing), header only - 220R each.
BOOT0: 10k down on the module. Close JP1001 at power-up for USB DFU (system bootloader on PA11/PA12).
